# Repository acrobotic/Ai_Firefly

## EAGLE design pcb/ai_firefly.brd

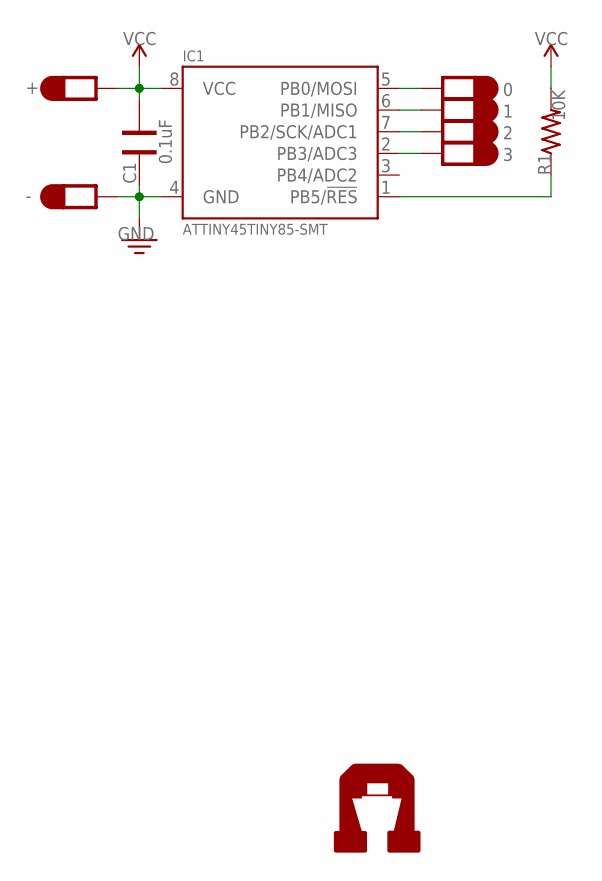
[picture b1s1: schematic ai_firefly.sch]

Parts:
0, 1, 2, 3: 1X01-PETAL
+: 1X01-PETAL
-: 1X01-PETAL
C1: 0.1uF; CAP-0603
IC1: ATTINY45TINY85-SMT; S008-EIAJ
R1: 10K; RES-0603
U$9: AI-LOGOXS; AI-LOGO-XS

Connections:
0: 0.1, IC1.5 (PB0/MOSI)
1: 1.1, IC1.6 (PB1/MISO)
2: 2.1, IC1.7 (PB2/SCK/ADC1)
3: 3.1, IC1.2 (PB3/ADC3)
GND: -.1, C1.2, IC1.4 (GND)
RES: IC1.1 (PB5/!RES), R1.1
VCC: +.1, C1.1, IC1.8 (VCC), R1.2

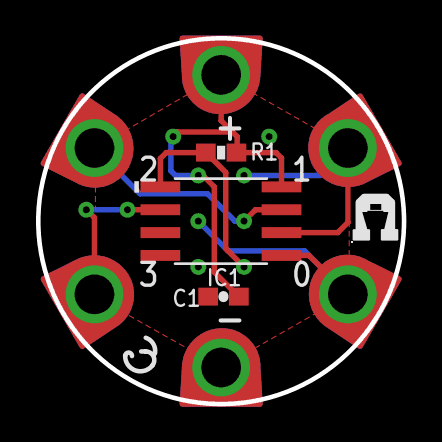
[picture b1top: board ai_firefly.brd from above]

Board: 2 copper layers, 20.3 x 20.3 mm, 10 parts (0 on the bottom side), 7 nets.

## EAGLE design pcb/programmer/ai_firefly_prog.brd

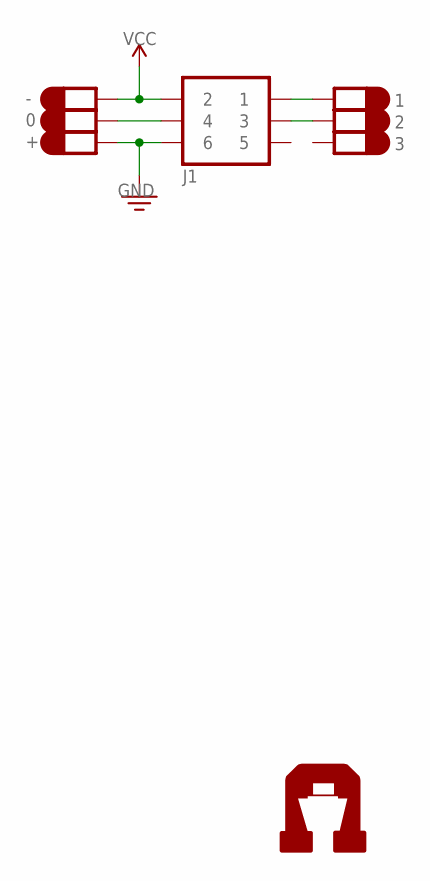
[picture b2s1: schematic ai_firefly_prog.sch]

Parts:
0, 1, 2, 3: 1X01-PETAL
+: 1X01-PETAL
-: 1X01-PETAL
J1: 2X03
U$9: AI-LOGOXS; AI-LOGO-XS

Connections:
0: 0.1, J1.4
1: 1.1, J1.1
2: 2.1, J1.3
GND: +.1, J1.6
VCC: -.1, J1.2

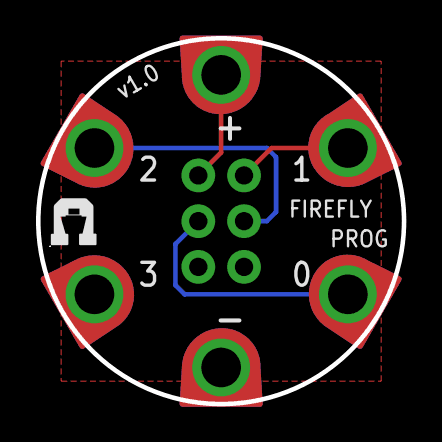
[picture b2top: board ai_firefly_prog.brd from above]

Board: 2 copper layers, 20.3 x 20.3 mm, 8 parts (1 on the bottom side), 5 nets.

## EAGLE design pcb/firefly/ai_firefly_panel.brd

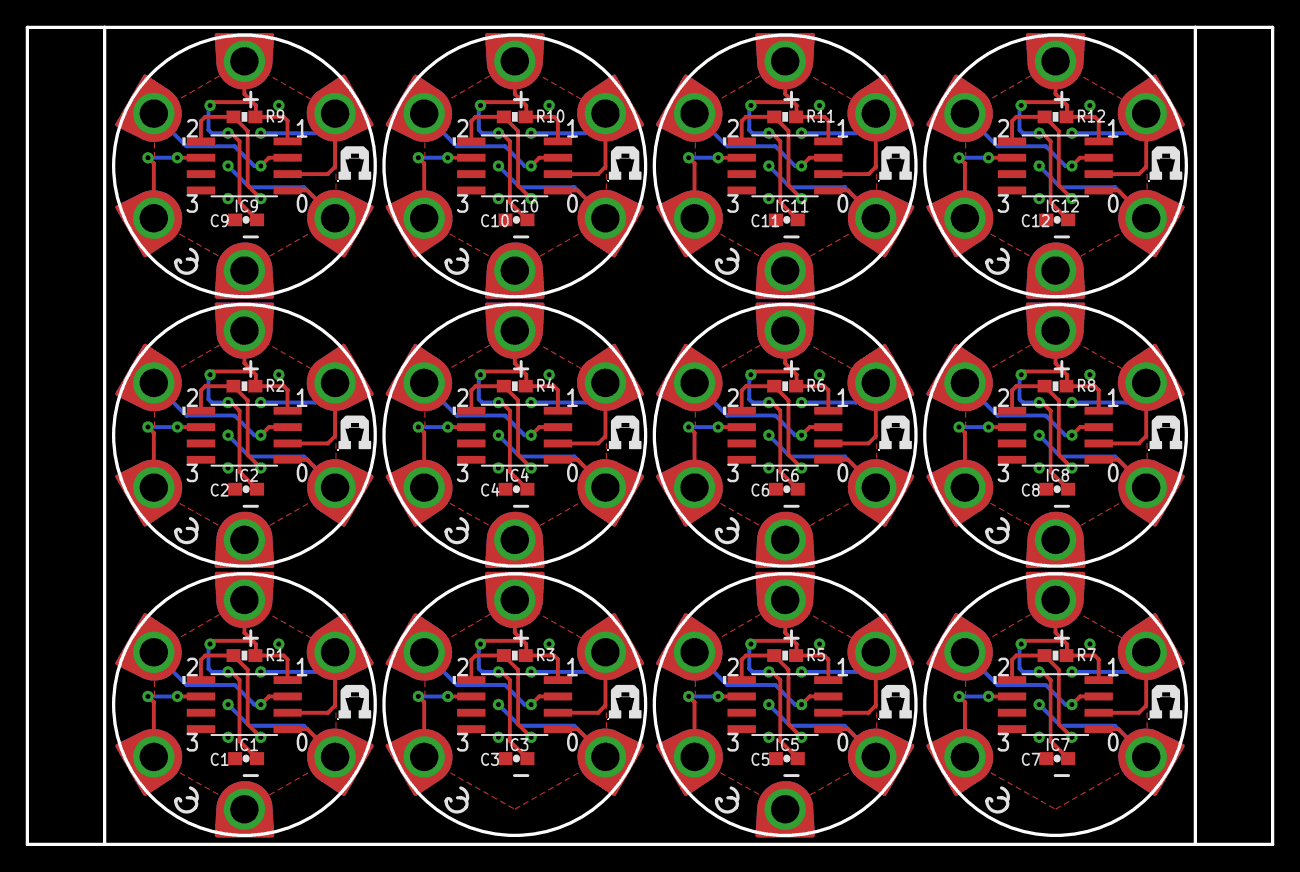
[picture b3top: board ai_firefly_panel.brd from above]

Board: 2 copper layers, 96.7 x 63.5 mm, 118 parts (0 on the bottom side), 84 nets.

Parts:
0, 1, 2, 3, 4, 5, 6, 7, 8, 9, 10, 11, 12, 13, 14, 15, 16, 17, 18, 19, 20, 21, 22, 23, 24, 25, 26, 27, 28, 29, 30, 31, 32, 33, 34, 35, 36, 37, 38, 39, 40, 41, 42, 43, 44, 45, 46, 47: 1X01-PETAL
+, +1, +2, +3, +4, +5, +6, +7, +8, +9, +10, +11: 1X01-PETAL
-, -1, -2, -3, -4, -5, -6, -7, -8, -9: 1X01-PETAL
C1, C2, C3, C4, C5, C6, C7, C8, C9, C10, C11, C12: 0.1uF; CAP-0603
IC1, IC2, IC3, IC4, IC5, IC6, IC7, IC8, IC9, IC10, IC11, IC12: ATTINY45TINY85-SMT; S008-EIAJ
R1, R2, R3, R4, R5, R6, R7, R8, R9, R10, R11, R12: 10K; RES-0603
U$1, U$2, U$3, U$4, U$5, U$6, U$7, U$8, U$9, U$10, U$11, U$12: AI-LOGOXS; AI-LOGO-XS

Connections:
0: 0.1, IC1.5
1: 1.1, IC1.6
2: 2.1, IC1.7
3: 3.1, IC1.2
4: 6.1, IC2.2
5: 7.1, IC2.7
6: 4.1, IC2.6
7: 5.1, IC2.5
8: 10.1, IC3.2
9: 11.1, IC3.7
10: 8.1, IC3.6
11: 9.1, IC3.5
12: 14.1, IC4.2
13: 15.1, IC4.7
14: 12.1, IC4.6
15: 13.1, IC4.5
16: 18.1, IC5.2
17: 19.1, IC5.7
18: 16.1, IC5.6
19: 17.1, IC5.5
20: 22.1, IC6.2
21: 23.1, IC6.7
22: 20.1, IC6.6
23: 21.1, IC6.5
24: 26.1, IC7.2
25: 27.1, IC7.7
26: 24.1, IC7.6
27: 25.1, IC7.5
28: 30.1, IC8.2
29: 31.1, IC8.7
30: 28.1, IC8.6
31: 29.1, IC8.5
32: 34.1, IC9.2
33: 35.1, IC9.7
34: 32.1, IC9.6
35: 33.1, IC9.5
36: 38.1, IC10.2
37: 39.1, IC10.7
38: 36.1, IC10.6
39: 37.1, IC10.5
40: 42.1, IC11.2
41: 43.1, IC11.7
42: 40.1, IC11.6
43: 41.1, IC11.5
44: 46.1, IC12.2
45: 47.1, IC12.7
46: 44.1, IC12.6
47: 45.1, IC12.5
GND: -.1, C1.2, IC1.4
GND1: -1.1, C2.2, IC2.4
GND2: C3.2, IC3.4
GND3: -2.1, C4.2, IC4.4
GND4: -3.1, C5.2, IC5.4
GND5: -4.1, C6.2, IC6.4
GND6: C7.2, IC7.4
GND7: -5.1, C8.2, IC8.4
GND8: -6.1, C9.2, IC9.4
GND9: -7.1, C10.2, IC10.4
GND10: -8.1, C11.2, IC11.4
GND11: -9.1, C12.2, IC12.4
RES: IC1.1, R1.1
RES1: IC2.1, R2.1
RES2: IC3.1, R3.1
RES3: IC4.1, R4.1
RES4: IC5.1, R5.1
RES5: IC6.1, R6.1
RES6: IC7.1, R7.1
RES7: IC8.1, R8.1
RES8: IC9.1, R9.1
RES9: IC10.1, R10.1
RES10: IC11.1, R11.1
RES11: IC12.1, R12.1
VCC: +.1, C1.1, IC1.8, R1.2
VCC1: +1.1, C2.1, IC2.8, R2.2
VCC2: +2.1, C3.1, IC3.8, R3.2
VCC3: +3.1, C4.1, IC4.8, R4.2
VCC4: +4.1, C5.1, IC5.8, R5.2
VCC5: +5.1, C6.1, IC6.8, R6.2
VCC6: +6.1, C7.1, IC7.8, R7.2
VCC7: +7.1, C8.1, IC8.8, R8.2
VCC8: +8.1, C9.1, IC9.8, R9.2
VCC9: +9.1, C10.1, IC10.8, R10.2
VCC10: +10.1, C11.1, IC11.8, R11.2
VCC11: +11.1, C12.1, IC12.8, R12.2

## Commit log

2014-05-28 First commit.
2014-06-11 updating pdf schematics
2014-12-23 moving jig pcb to different repo
2016-04-01 updating firmware
